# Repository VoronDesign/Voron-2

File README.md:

# Voron 2.4

### Download the STLs

Older releases, single parts and a 3D preview: **[voron.zip](https://voron.zip/#m=v2)**

The official release of the Voron 2.4 3d printer.  You can find the BOM in the configurator located at the [Voron Design]( http://vorondesign.com/voron2.4) website.

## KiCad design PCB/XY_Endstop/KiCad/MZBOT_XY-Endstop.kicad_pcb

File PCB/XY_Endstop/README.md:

XY Endstop

# MZBOT XY Endstop
Hall effect endstop board for X and Y axes

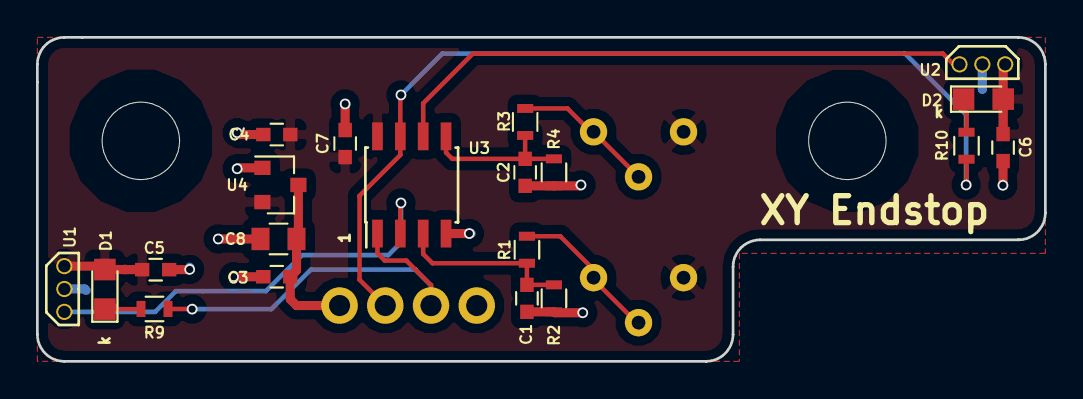
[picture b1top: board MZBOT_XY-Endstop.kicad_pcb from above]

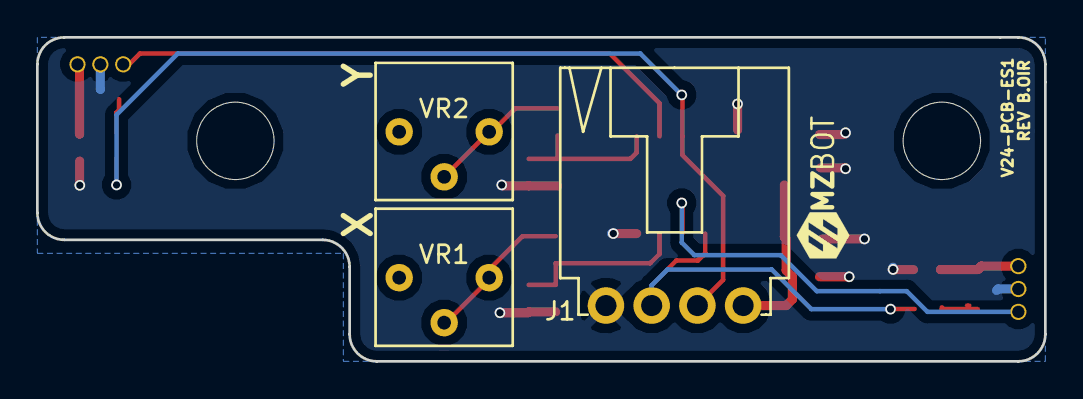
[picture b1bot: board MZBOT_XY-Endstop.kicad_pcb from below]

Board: 2 copper layers, 56.0 x 18.0 mm, 23 parts (3 on the bottom side), 13 nets.

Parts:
C1, C2: 0.1uF; C_0603
C3, C4, C5, C6, C7: 1uF; C_0603
C8: 10uF; C_0805
D1, D2: LED_0805
J1: CONN_01X04; 1X4_CONN_L_RA
R1, R3, R9, R10: 1.00K; R_0603
R2, R4: 10.0k; R_0603
U1, U2: SS49E; SIP-3
U3: LM393; SOIC-8_3.9x4.9mm_Pitch1.27mm
U4: AP2210N; SOT-23
VR1, VR2: 10.0K; CT6EP103

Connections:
+3V3: C4.1, C5.1, C6.1, C7.2, D1.2, D2.2, U1.1, U2.1, U3.8, U4.2, VR1.3, VR2.3
+5V: C3.1, C8.1, J1.4, U4.3
GND: C1.2, C2.2, C3.2, C4.2, C5.2, C6.2, C7.1, C8.2, J1.1, R2.2, R4.2, U1.2, U2.2, U3.4, U4.1
unnamed: C1.1, R1.1, R2.1, U3.3
unnamed: C2.1, R3.1, R4.1, U3.5
unnamed: D1.1, R9.1
unnamed: D2.1, R10.1
unnamed: R1.2, VR1.1, VR1.2
unnamed: R3.2, VR2.1, VR2.2
unnamed: U1.3, U3.2
unnamed: U2.3, U3.6
X_SIG: J1.2, R9.2, U3.1
Y_SIG: J1.3, R10.2, U3.7

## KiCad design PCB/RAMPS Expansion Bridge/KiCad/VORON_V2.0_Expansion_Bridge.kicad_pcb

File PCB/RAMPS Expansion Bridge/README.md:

# VORON V2-Expansion Bridge
Expansion PCB to bridge the VORON Expander and a RAMPS 1.4

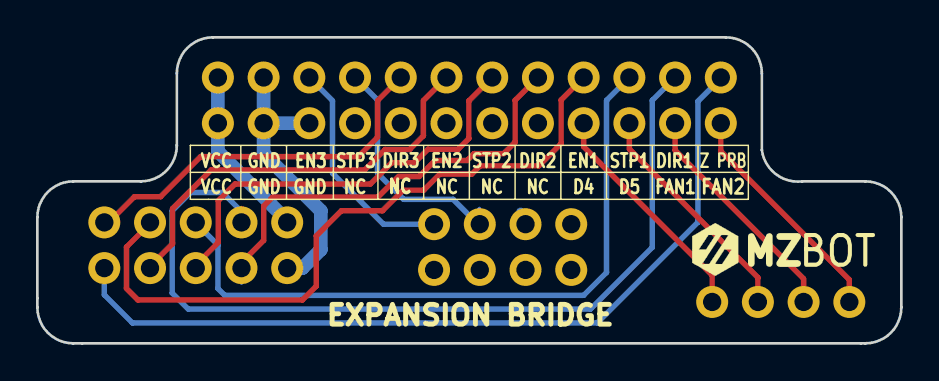
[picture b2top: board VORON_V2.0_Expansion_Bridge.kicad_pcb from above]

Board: 2 copper layers, 48.0 x 17.0 mm, 4 parts (0 on the bottom side), 16 nets.

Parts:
J1: PIN_SOCKET_BOTTOM_1X4
J2: CONN_02X04; PIN_SOCKET_BOTTON_2X4
J3: CONN_02X05; PIN_SOCKET_BOTTOM_2X5
J4: CONN_02X12; PIN_SOCKET_BOTTON_2X12

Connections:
D4: J1.1, J4.17
D5: J1.2, J4.19
DIR_1(A5/D59): J3.3, J4.22
DIR_2(A9/D63): J3.4, J4.16
DIR_3(A12/D66): J3.9, J4.10
EN_1(D44): J3.7, J4.18
EN_2(D42): J3.8, J4.12
EN_3(A4/D58): J2.7, J4.6
FAN1(D11): J1.4, J4.23
FAN2(D6): J1.3, J4.21
GND: J3.2, J4.3, J4.4, J4.5
STEP_1(A10/D64): J3.5, J4.20
STEP_2(D48): J3.6, J4.14
STEP_3(A3/D57): J2.5, J4.8
VCC: J3.1, J4.1, J4.2
Z_PROBE(A11/D65): J3.10, J4.24

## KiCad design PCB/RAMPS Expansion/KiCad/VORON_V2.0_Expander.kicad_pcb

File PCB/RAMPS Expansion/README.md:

# VORON V2-Expander
Expansion PCB to add 3 additional stepper drivers, 2 external PWM fans, and induction probe port to a standard RAMPS 1.4 shield

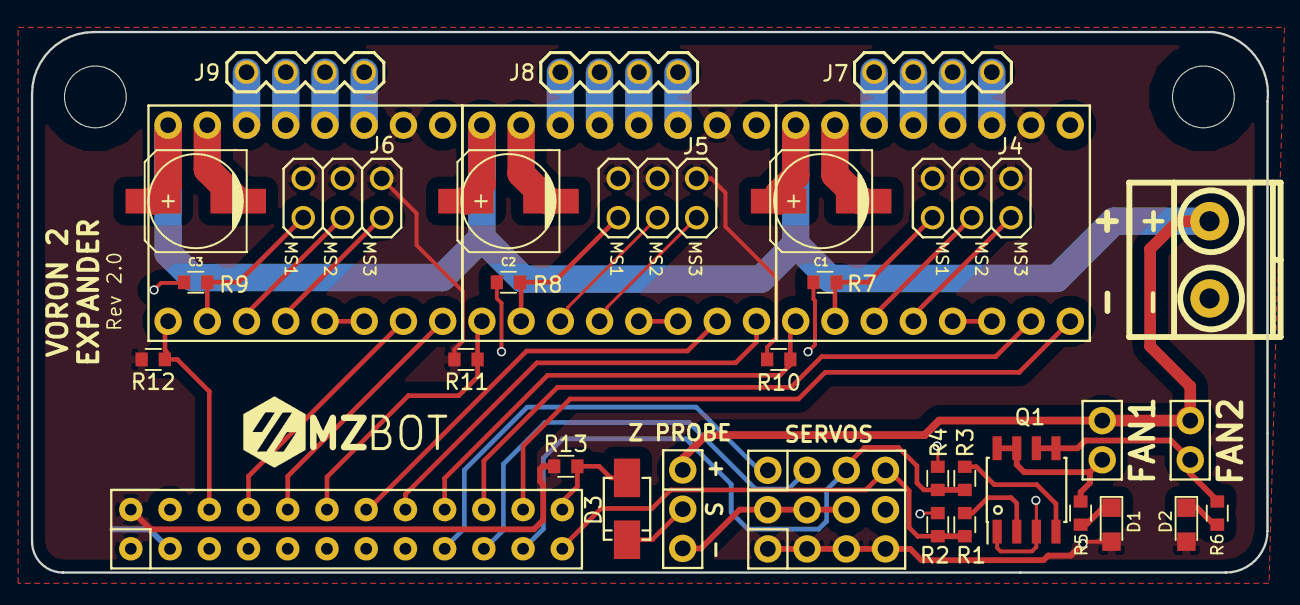
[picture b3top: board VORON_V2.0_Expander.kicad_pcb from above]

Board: 2 copper layers, 80.0 x 35.0 mm, 36 parts (0 on the bottom side), 48 nets.

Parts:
C1, C2, C3: 100uF; c_elec_6.3x7.7
D1, D2: LED; LED_0805
D3: D_Small; SMA_Diode
FAN1: FAN1; PIN_HEADER_TOP_1X2
FAN2: FAN2; PIN_HEADER_TOP_1X2
J4, J5, J6: CONN_02X03; 2X03_PIN_HEADER
J7: Stepper 1; 1X04_PIN_HEADER
J8: Stepper 2; 1X04_PIN_HEADER
J9: Stepper 3; 1X04_PIN_HEADER
P1: CONN_02X12; PIN_HEADER_TOP_2X12
P2: CONN_01X04; PIN_HEADER_TOP_1X4
P3: CONN_01X03; PIN_HEADER_TOP_1X3
P4: CONN_02X04; PIN_HEADER_TOP_2x4
PWRIN1: PWRIN; mkds_1,5-2
Q1: IRF8313PBF; SOIC-8_3.9x4.9mm_Pitch1.27mm
R1, R3: 100; R_0603
R2, R4, R7, R8, R9: 100k; R_0603
R5, R6: 1.80k; R_0603
R10, R11, R12, R13: 10.0k; R_0603
Stepstick1, Stepstick2, Stepstick3: Stepstick; Steppers

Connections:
D4: P1.17, P2.1
D5: P1.19, P2.2
DIR_1(A5/D59): P1.22, Stepstick1.8
DIR_2(A9/D63): P1.16, Stepstick2.8
DIR_3(A12/D66): P1.10, Stepstick3.8
EN_1(D44): P1.18, R10.2, Stepstick1.1
EN_2(D42): P1.12, R11.2, Stepstick2.1
EN_3(A4/D58): P1.6, R12.2, Stepstick3.1
FAN1(D11): P1.23, P2.4, R1.2, R2.2
FAN2(D6): P1.21, P2.3, R3.2, R4.2
GND: C1.2, C2.2, C3.2, P1.3, P1.5, P3.3, P4.2, P4.4, P4.6, P4.8, PWRIN1.1, Q1.1, Q1.3, R2.1, R4.1, R7.1, R8.1, R9.1, Stepstick1.9, Stepstick1.15, Stepstick2.9, Stepstick2.15, Stepstick3.9, Stepstick3.15
unnamed: D1.1, R5.2
unnamed: D2.1, R6.2
unnamed: D3.1, P3.2
unnamed: FAN1.2, Q1.7, Q1.8, R5.1
unnamed: FAN2.2, Q1.5, Q1.6, R6.1
unnamed: J4.1, R7.2, Stepstick1.2
unnamed: J4.3, Stepstick1.3
unnamed: J4.5, Stepstick1.4
unnamed: J5.1, R8.2, Stepstick2.2
unnamed: J5.3, Stepstick2.3
unnamed: J5.5, Stepstick2.4
unnamed: J6.1, R9.2, Stepstick3.2
unnamed: J6.3, Stepstick3.3
unnamed: J6.5, Stepstick3.4
unnamed: J7.1, Stepstick1.14
unnamed: J7.2, Stepstick1.13
unnamed: J7.3, Stepstick1.12
unnamed: J7.4, Stepstick1.11
unnamed: J8.1, Stepstick2.14
unnamed: J8.2, Stepstick2.13
unnamed: J8.3, Stepstick2.12
unnamed: J8.4, Stepstick2.11
unnamed: J9.1, Stepstick3.14
unnamed: J9.2, Stepstick3.13
unnamed: J9.3, Stepstick3.12
unnamed: J9.4, Stepstick3.11
unnamed: Q1.2, R1.1
unnamed: Q1.4, R3.1
unnamed: Stepstick1.5, Stepstick1.6
unnamed: Stepstick2.5, Stepstick2.6
unnamed: Stepstick3.5, Stepstick3.6
STEP_1(A10/D64): P1.20, Stepstick1.7
STEP_2(D48): P1.14, Stepstick2.7
STEP_3(A3/D57): P1.8, Stepstick3.7
VCC: D1.2, D2.2, J4.2, J4.4, J4.6, J5.2, J5.4, J5.6, J6.2, J6.4, J6.6, P1.1, P1.2, P4.1, P4.3, P4.5, P4.7, R10.1, R11.1, R12.1, R13.1, Stepstick1.10, Stepstick2.10, Stepstick3.10
VMOT: C1.1, C2.1, C3.1, FAN1.1, FAN2.1, P3.1, PWRIN1.2, Stepstick1.16, Stepstick2.16, Stepstick3.16
Z_PROBE(A11/D65): D3.2, P1.24, R13.2

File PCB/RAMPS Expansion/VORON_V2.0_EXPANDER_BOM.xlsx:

Title | VORON V2.0 Expander
Company | MZBOT
Revision | B
Date Issue | 42739.926041666666
Quantity | Reference | Description | Manufacture | Manufacture P/N | Digi-Key | Price @ 1 | Price @ 100
1 | P1 | CONN HEADER 24POS 2.54 STR 15AU | Amphenol FCI | 67997-224HLF | 609-3395-ND | 0.91 | 0.69230000000000003
4 | P2, J7, J8, J9 | CONN HEADER 4 POS 2.54 | Wurth Electronics Inc. | 61300411121 | 732-5317-ND | 0.18 | 9.6000000000000002E-2
3 | J4, J5, J6 | CONN HEADER 6 POS 2.54 | Harwin Inc. | M20-9980346 | 952-2121-ND | 0.24 | 0.15859999999999999
2 | FAN1, FAN2 | CONN HEADER 2 POS 2.54 | Harwin Inc. | M20-9990246 | 952-2262-ND | 0.11 | 6.0900000000000003E-2
1 | P3 | CONN HEADER 3 POS 2.54 | Wurth Electronics Inc. | 61300311121 | 732-5316-ND | 0.15 | 6.7000000000000004E-2
1 | P4 | CONN HEADER 8 POS 2.54 | Harwin Inc. | M20-9980446 | 952-2123-ND | 0.3 | 0.19600000000000001
1 | PWRIN1 | TERM BLOCK 2POS 5.08MM PCB HORIZ | Amphenol Anytek | VI0221520000G | 609-3936-ND | 0.88 | 0.4113
3 | C1, C2, C3 | CAP ALUM 100UF 20% 35V SMD | Nichicon | UWT1V101MCL1GS | 493-2203-1-ND | 0.39 | 0.1641
2 | R1, R3, | RES SMD 100 OHM 1% 1/10W 0603 | Yageo | RC0603FR-07100RL | 311-100HRCT-ND | 0.1 | 6.0000000000000001E-3
5 | R2, R4, R7, R8, R9 | RES SMD 100K OHM 1% 1/10W 0603 | Yageo | RC0603FR-07100KL | 311-100KHRCT-ND | 0.1 | 6.0000000000000001E-3
2 | R5, R6, | RES SMD 1.8K OHM 1% 1/10W 0603 | Yageo | RC0603FR-071K8L | 311-1.80KHRCT-ND | 0.1 | 6.0000000000000001E-3
4 | R10, R11, R12, R13 | RES SMD 10K OHM 1% 1/10W 0603 | Yageo | RCRC0603FR-0710KL | 311-10.0KHRCT-ND | 0.1 | 6.0000000000000001E-3
1 | Q1 | MOSFET 2N-CH 30V 9.7A 8-SOIC | Infineon Technologies | IRF8313TRPBF | IRF8313TRPBFCT-ND | 0.77 | 0.51800000000000002
6 | Stepstick1, Stepstick2, Stepstick3, (x2 each) | CONN HEADER FEMALE 8 POS 2.54 | Sullins Connector Solutions | PPTC081LFBN-RC | S7006-ND | 0.65 | 0.46579999999999999
2 | D1, D2 | LED RED DIFFUSED 0805 SMD | OSRAM Opto Semiconductors Inc. | LS R976-NR-1 | 475-1278-1-ND | 0.26 | 9.98E-2
1 | D3 | DIODE SCHOTTKY 60V 1A SMA | Diodes Incorporated | B160-13-F | B160-FDICT-ND | 0.37 | 0.1615
9 |  | CONN JUMPER SHORTING TIN | Sullins Connector Solutions | STC02SYAN | S9000-ND | 0.1 | 3.6499999999999998E-2
1 |  | PCB | MZBOT |  | - | 0.49 | 0.2732

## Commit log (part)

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2020-06-30 New version
2020-07-04 Voron 2.1 cad added (#156)
    * Create Readme.md
    * Create VORON 2.1 Assembly.step.zip
2020-07-07 Update with JST version
2020-07-25 rearrange files
2020-07-25 Add Doc's Profiles
2020-08-01 update neopixel title
2020-08-02 Updated Z stepper mounts (#174)
    Revised part for more strength and better print orientation.
2020-08-02 Revert "Files repaired. Fixes issue #125"
    This reverts commit d0c435525ba87bc1024418adbb3205bb80a6ec45.
2020-08-05 Add files via upload
    Collection of changes based on suggestions from #v24_manual
2020-08-09 Removed whitespaces from directory names
2020-08-10 2020.08.05 Update (#178)
    * Delete 2.4_Assembly_Manual.pdf
    Remove
    * Add files via upload
    Collection of changes based on suggestions from #v24_manual
2020-08-22 no more mirrored logo on voron cube (#183)
2020-09-24 Fix setdisplayneopixel macro on SKR1.4 config
2020-09-29 Fix setdisplayneopixel macros on SKR1.3 and 1.4 configs. (#189)
    * Fix setdisplayneopixel macro on SKR1.4 config
    * Fix setdisplayneopixel macro on SKR1.3
2020-11-01 As of 29OCT2020 color_order_GRB is no longer a supported option in the klipper master branch
2020-11-27 restores working STL revision under updated name
    Issue #167 broke the STL file
    A file rename should not have added ~100KB of data and broken the STL
    for usage.
    This commit reverts the file to its previously working state under the
    new filename identified in issue #167.
2020-12-09 Add github workflow
2020-12-09 Fix for several issues (#125) (#201) (#198)
    * Updated Z stepper mounts
    Revised part for more strength and better print orientation.
    * Files repaired. Fixes issue #125
    * Revert "Files repaired. Fixes issue #125"
    This reverts commit d0c435525ba87bc1024418adbb3205bb80a6ec45.
    * Files repaired. Fixes issue #125
2021-01-09 stock config updates
    * updated V2 SKR 1.3 Config to use rotation_distance in place of step_distance
    * updated V2 SKR 1.3 Config to use by-id serial paths in place of by-path
2021-01-09 update manual (#204)
2021-01-18 SKR update
2021-02-06 update manual (#208)
2021-02-07 matching changes to skr1.3
2021-03-13 Update Voron2_SKR_14_Config.cfg
    revised to use SAFE_Z_HOME instead of HOMING_OVERRIDE
    Note: this also involved moving the final toolhead position move to the G32 macro, and making G32 the default action in the PRINT_START macro, rather than G28
    Ideally, merge should be done roughly in sync with updated documentation going live.
2021-03-13 Update Voron2_SKR_13_Config.cfg
    matching changes to SKR 1.4 update
2021-03-22 renamed skr bracket for clarity
2021-04-21 Updated skirt files. Modified M3 holes for better T-nut thread engagement.
2021-04-28 Create Heatset_Practice.stl
    some users were saying how they would like a heatset practice piece so they done ruin a PIF part , so I drew this piece up which works well, its got 7 4.7mm diameter holes that are 5mm deep in differ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
2021-05-03 Renamed exhaust_filter_mount_x2.stl -> [a]_exhaust_filter_mount_x2.stl. Fixes issue #224
2021-05-04 Updated [a]_endstop_pod_microswitch.stl for more switch clearance. Fixes issue #136
2021-05-04 Updated CAD with latest changes
2021-05-04 Fix caselight in SKR1.4 config (#230)
    Change Caselight value from 100 -> 1
2021-05-04 Corrected missing fillet on a_drive_frame_upper.stl
2021-05-04 Add missing fillet to A drive, fix motor orientation in CAD
2021-07-11 Created draft config for V2 Spider
2021-07-14 Fixed comment for pin definition of NO probes (#244)
2021-07-17 Fix zip archive.
2021-08-09 Add documentation for the test prints.
2021-08-13 Update voron cube instructions with pin from gchat
2021-08-16 Update Voron2_Spider_Config.cfg
    Removed rogue pixel count
2021-09-03 Update Voron2_Spider_Config.cfg
    a few small cleanups to Spider printer.cfg
2021-09-14 Recreate zip file for CAD
2021-09-16 Add the Afterburner pulley jig
2021-09-27 Add reference config file for BTT Octopus board
2021-10-08 Fix CAD zip archive (#265)
    * Fix zip archive.
    * Recreate zip file for CAD
    * Make 300/350 Skirts visable in F3D so they export to step
2021-11-14 Fix variable names
2021-11-22 fixed error caused by controller_fan config.
2021-11-24 Add note about updating thermistor types for heaters.
2021-11-28 Remove Afterburner STLs from v2 repo to reduce upkeep work.
2021-11-30 Comment out PA values
2021-12-06 Fix capitalization.
2021-12-22 fix missing double # on some comments.
2021-12-24 Add Monster8 example config
2021-12-30 Remove leading spaces from selectable config options that could lead to klipper errors if user is not familiar with config syntax.
2022-01-19 fix default z stepper directions.
2022-01-21 Add G90 before G0 in G32 macro
2022-02-01 Remove bed_mesh_clear from g32 in v2 configs.
2022-02-06 fix a typo in What_the_git.md
2022-02-15 LICENSE: Remove the wrong file extension
    This license is not formatted in markdown which causes GitHub and alike
    to format it weirdly, thus this commit removes the extension.
    Alternatively there is an option of using
    https://github.com/TheFox/GPLv3.md which converted the license in
    markdown formatting.
2022-02-19 add SSR option for other wire harness (#310)
    * add SSR option for other wire harness
    * update comments
2022-02-19 Updated assembly manual for Voron 2.4r2 release. Fixes issues #229, #237, #260, #267, #273, #276, #277, and #298
2022-02-19 Updated panel and build plate drawings and DXFs.
2022-02-19 Update to 5mm@30mm/s
2022-02-20 Corrected extra zip tie mounts on the Revo Micro Toolhead.
2022-02-20 Updated assembly manual with minor typo and grammar corrections.
2022-02-21 Updated file names on test print STLs.
2022-02-22 Updating CAD assembly for V2.4r2
2022-02-23 Added G90 to PRINT_START macro
2022-02-23 Removed RAMPS configuration examples.
2022-02-23 Added optional extruder_motor_plate that includes a heatset spot for toolhead PCB mounting.
2022-02-24 update of manual files
    various pages: changed wording based on community feedback
    various pages: fixed hyperlinks
    page 122: added note to remove zipties
    page 237: fixed probe wire colours
    page 243: added missing callout for heatset inserts
    page 288: added missing t-nut insertion
2022-02-26 Octopus config: Run hotend fan in case of shutdown
    In case the MCU is shutdown from any kind of failure, it is good practice to have the hotend fan running to make sure we get no heat creep in the heatbreak.
2022-02-27 Switch electronics cooling fan from a `heater_fan` to a `controller_fan`
    Switch to using the `controller_fan` module for the electronics cooling fans on the SKR1.3, SKR1.4, & Spider Klipper Configs
2022-03-06 Update manual files (#326)
    various pages: changed wording based on community feedback
    page 234 - added missing accent callout
    page 266 - fixed inductive probe wiring
2022-04-04 Added a BOM, exported from the Fusion 360 assembly
2022-04-08 manual update
    page 98 Pulley -> Idler
    page 100 Pulley -> Idler
    page 197 added missing t-nut
    page 220 split pwr in, added note about bed out
    page 242 added side fan support heatset
    page 270 added part highlight
2022-04-20 Update Voron2_SKR_14_Config.cfg
    Update the heater_bed sensor to be the more accurate algorithm "Generic 3950"
2022-04-22 Remove default sensor_types
2022-04-23 Remove 3950 footnotes, ensure newlines at end of configs
2022-05-04 Remove 20mm from 250/350 too
2022-05-05 Update Voron2_Spider_Config.cfg (#354)
    Remove space from end of output_pin config section
2022-05-08 Manual update (#356)
    Removed diagram from page 206
2022-07-04 Manual Update 2022-07-04
    page 8 - fixed spelling
    page 106 - changed callout text for the bolts on the right xy joint
    page 122 - changed callout text to include rear brace adjustment
    page 206 - updated diagram
    page 210 - updated graphic to reflect actual position of the PE lug
    page 210 - updated graphic to reflect actual position of the PE lug
2022-07-04 Update Z max position (#352)
    * Update Z max position
    280mm is enough to crash the gantry in the top of the printer. Lowered it to 260 to prevent this.
    * Remove 20mm from 250/350 too
2022-08-06 add revo voron printheads (#379)
    * Create Readme.md
    * Add files via upload
    * Delete Readme.md
2022-09-29 Update Voron2_Octopus_Config.cfg
    further cleanups
2022-09-29 Shiftingtech display order (#391)
    * Update Voron2_Octopus_Config.cfg
    swapped comments and headers in the display sections, to hopefully reduce user confusion
    * Update Voron2_SKR_13_Config.cfg
    style change for consistent placement of description before section header
    * Update Voron2_Octopus_Config.cfg
    further cleanups
2022-10-04 Removing Cura binaries (#393)
2022-11-11 Update PSU_stabilizer_50mm.stl
    Updated to match current CAD
2022-11-11 Fixed STL orientation
2022-12-13 Added Gear Ratio for CW2 to printer.cfg (#397)
    * Added Gear Ratio for CW2
    * Added Gear Ratio for CW2
    * Added Gear Ratio for CW2
    * Added Gear Ratio for CW2
    * Added Gear Ratio for CW2
    * Added Gear Ratio for CW2
2022-12-28 Update Voron2_SKR_14_Config.cfg
    updated print end and g32 to use the printer.toolhead object so you no longer need to uncomment what size printer you are building as well as added a park macro
2023-01-11 Make quad gantry leveling safer for new builds
2023-03-03 cad file upload
2023-03-03 Correct probe inversion comment (#314)
    The comment in the SKR1.4 file uses the incorrect syntax for inverting the probe connection (at least as of current klipper).
    The ! and ^ were transposed.
2023-04-06 slight cleanup
2023-06-15 Update CI dependencies. (#434)
2023-07-05 manual
2023-09-03 updated CW2 chain anchor and fixed XY chain in cad assembly
2023-09-09 Update Voron2_Octopus_Config.cfg
    Change bed_heater formula to insure max_power doesn't exceed SSR rating.
2023-09-09 Update Voron2_SKR_14_Config.cfg
    Change bed_heater formula to insure max_power doesn't exceed SSR rating.
2023-09-09 Update config files to reflect SSR rating instead of the old, incorrect "warp" rating. (#448)
    * Update Voron2_M8P_config.cfg
    Change bed_heater formula to insure max_power doesn't exceed SSR rating.
    * Update Voron2_Octopus_Config.cfg
    Change bed_heater formula to insure max_power doesn't exceed SSR rating.
    * Update Voron2_SKR_13_Config.cfg
    Change bed_heater formula to insure max_power doesn't exceed SSR rating.
2023-10-29 Update Voron2_Octopus_Config.cfg (#453)
2023-11-22 Fix config file consistency and clarify GCode state command usage (#136)
    The PRINT_END macro in the Octopus config file contains a pair of
    SAVE_GCODE_STATE/RESTORE_GCODE_STATE command. The purpose of those
    commands is to allow the macro to perfom actions at the end of the
    print and then restore the printer state as it was prior to the
    macro's execution (restore coordinate system and speeds).
    However, there was some confusion as to the effect of those calls,
2024-01-21 Rename [a]_z_tensioner_x4_9mm.stl to [a]_z_tensioner_9mm_x4.stl
2024-01-23 Add a speed to the PARK macro, without it the speed is random and sometimes extremely slow
2024-03-15 Rename Voron2_M8P_config.cfg to Voron2_M8P-v1.0_config.cfg
    This is the M8P v1.0 pinout (check stepper_z2 on motor 6 to confirm the difference.
2024-09-16 Voron2_M8P-v2.0_config.cfg oops
2025-04-10 update assignments from equals to colon
2025-05-30 Bugfix: Correct dir_pin on stepper_z1 and stepper_z2 (#489)
    * Correct dir_pin on stepper_z1 and stepper_z2
    Tried moving gantry up using sample config. The front side moved up and the back side moved down.
    Checked other sample configs and found ! on dir_pin normally look similar between motors z and z2, and motors z1 and z3. Previous commit has ! on dir_pin similar between motors z and z1, and the moto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
    Swapping the ! on dir_pin on z1 and z2 corrects the issue
